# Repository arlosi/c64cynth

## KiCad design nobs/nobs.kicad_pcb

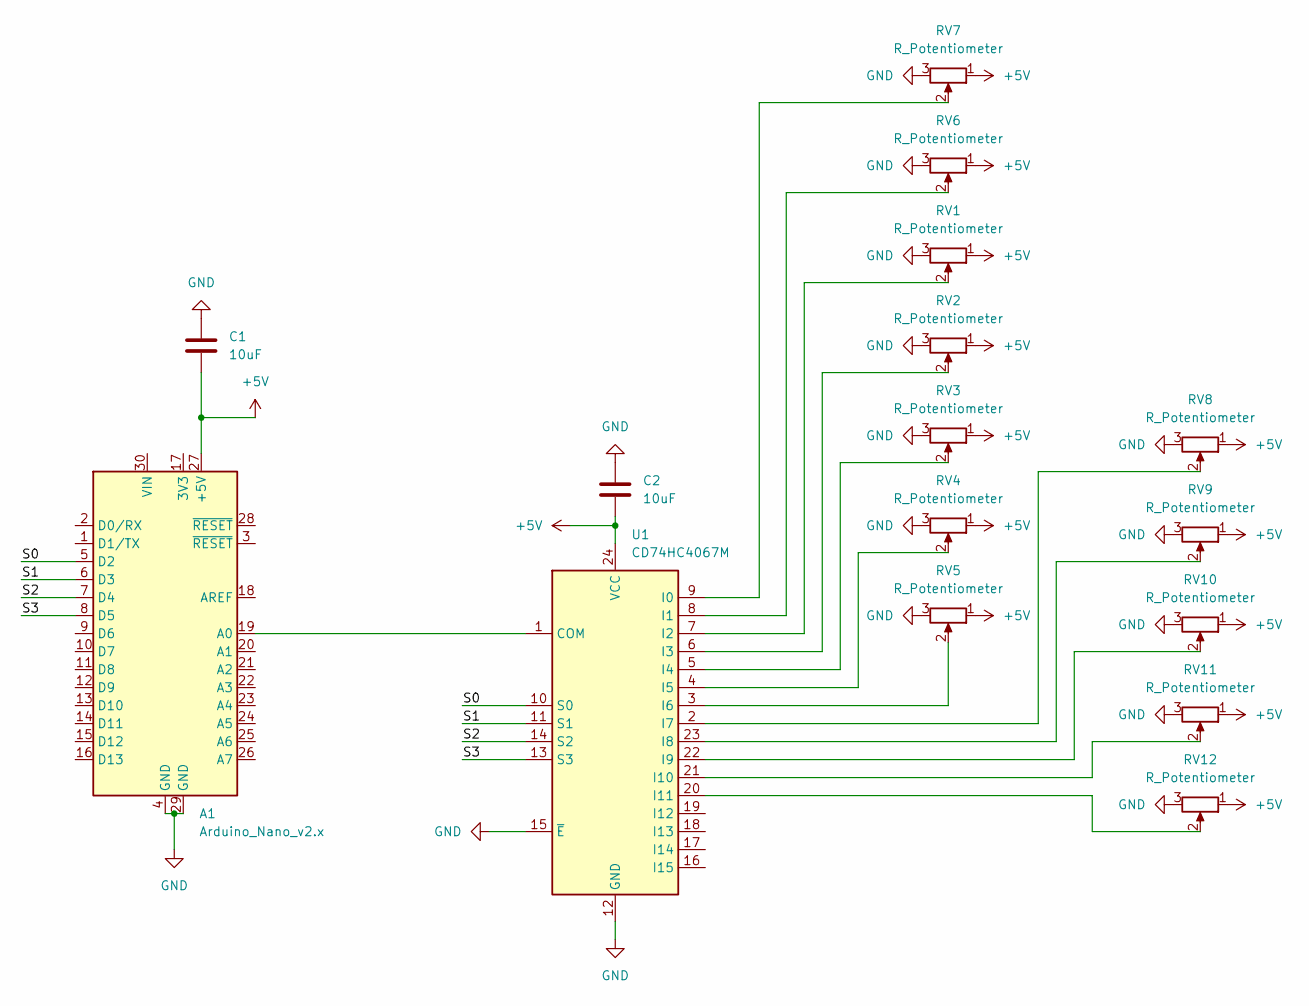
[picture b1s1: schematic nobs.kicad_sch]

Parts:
A1: Arduino_Nano_v2.x; Arduino_Nano
C1, C2: 10uF; C_0603_1608Metric_Pad1.08x0.95mm_HandSolder
RV1, RV2, RV3, RV4, RV5, RV6, RV7, RV8, RV9, RV10, RV11, RV12: R_Potentiometer; Potentiometer_Alpha_RD902F-40-00D_Dual_Vertical
U1: CD74HC4067M; SOIC-24W_7.5x15.4mm_P1.27mm

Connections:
+5V: A1.27 (+5V), C1.2, C2.2, RV1.1, RV2.1, RV3.1, RV4.1, RV5.1, RV6.1, RV7.1, RV8.1, RV9.1, RV10.1, RV11.1, RV12.1, U1.24 (VCC)
/S0: A1.5 (D2), U1.10 (S0)
/S1: A1.6 (D3), U1.11 (S1)
/S2: A1.7 (D4), U1.14 (S2)
/S3: A1.8 (D5), U1.13 (S3)
GND: A1.4 (GND), A1.29 (GND), C1.1, C2.1, RV1.3, RV2.3, RV3.3, RV4.3, RV5.3, RV6.3, RV7.3, RV8.3, RV9.3, RV10.3, RV11.3, RV12.3, U1.12 (GND), U1.15 (~E)
unnamed: A1.19 (A0), U1.1 (COM)
unnamed: RV7.2, U1.9 (I0)
unnamed: RV6.2, U1.8 (I1)
unnamed: RV1.2, U1.7 (I2)
unnamed: RV2.2, U1.6 (I3)
unnamed: RV3.2, U1.5 (I4)
unnamed: RV4.2, U1.4 (I5)
unnamed: RV5.2, U1.3 (I6)
unnamed: RV8.2, U1.2 (I7)
unnamed: RV9.2, U1.23 (I8)
unnamed: RV10.2, U1.22 (I9)
unnamed: RV11.2, U1.21 (I10)
unnamed: RV12.2, U1.20 (I11)

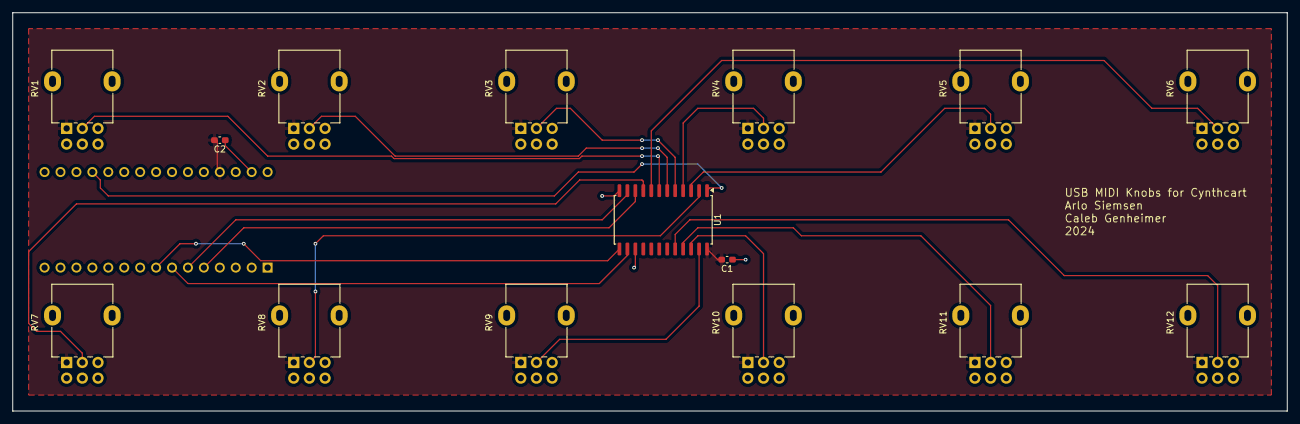
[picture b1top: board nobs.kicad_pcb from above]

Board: 2 copper layers, 203.2 x 63.5 mm, 16 parts (1 on the bottom side), 19 nets.
